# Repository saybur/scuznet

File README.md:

scuznet
=======

This is a modified version of the Scuznet board designed to fit in a
PowerBook. Also included is a small PCB for a PowerBook 100's modem 
bay. Otherwise this is fully compatible with a Scuznet V2.

Open source hardware emulating SCSI hard drives and an Ethernet adapter, for
use with vintage Macintosh computers.

# Status

The firmware is at a beta stage. There are things that are known to not work
correctly, and there are likely a large number of other bugs that have yet to
be identified and/or fixed.

If you encounter problems, please open a new issue.

# Compatibility

This implementation has some limitations by design:

1. There must be only one initiator on the bus.
2. The initiator on the bus must be at ID 7.
3. Read parity is not used. Transmission parity is provided but may be disabled
   to improve performance.

These should not be a significant problem for the target computer platform,
which for the most part has similar limitations.

# License

Except where otherwise noted, all files in this repository are available under
the terms of the GNU General Public License, version 3, available in the
LICENSE document. There is NO WARRANTY, not even for MERCHANTABILITY or
FITNESS FOR A PARTICULAR PURPOSE. For details, refer to the license.

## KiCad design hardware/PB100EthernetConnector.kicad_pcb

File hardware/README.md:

scuznet hardware
================

Provided here solely for informational purposes is a prototype hardware design
that was built for testing the scuznet firmware. This is the second revision
of the hardware, which has the following known issues.

* A USB connection is provided but there is (as yet) no hardware support for
  it. I must have lost my mind when selecting this part, it is a PITA to
  solder. Version 2.1 of the board should replace this with something easier
  to work with.
* The power connector footprint is still too big and wiggles around while
  soldering.

This version has not received significant testing yet.

# License

These files are available under the terms of the GNU General Public License,
version 3, available in the LICENSE document in the parent directory. There is
NO WARRANTY, not even for MERCHANTABILITY or FITNESS FOR A PARTICULAR PURPOSE.
For details, refer to the license.

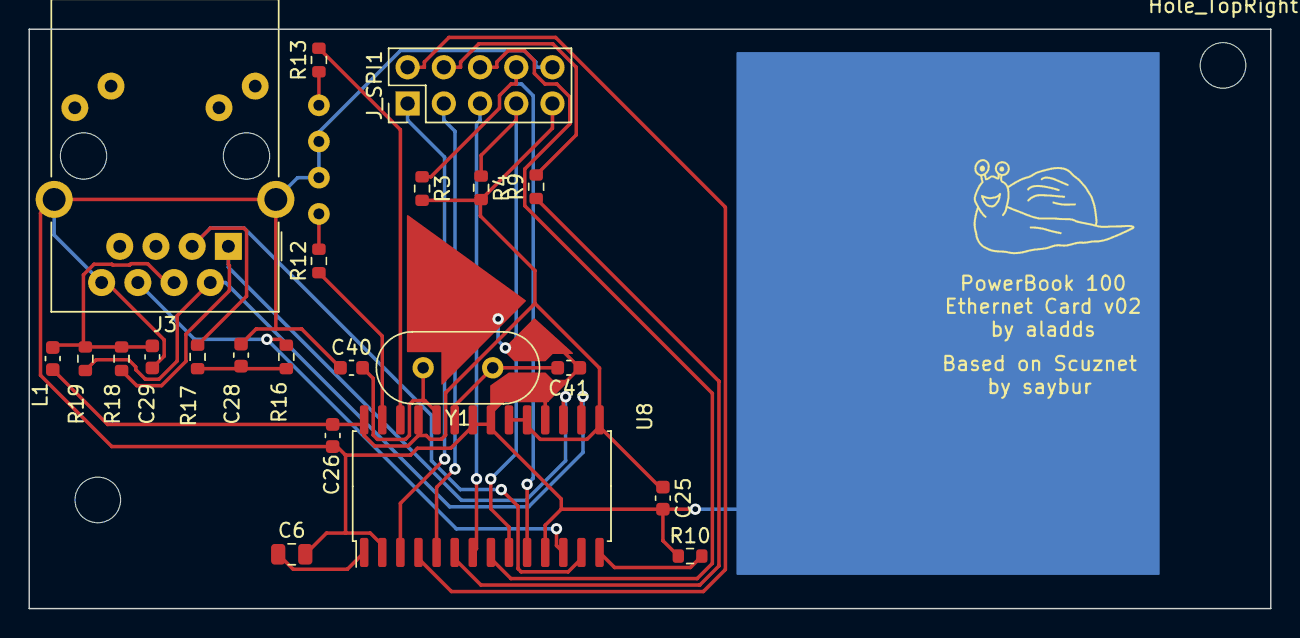
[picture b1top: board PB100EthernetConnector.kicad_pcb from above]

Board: 2 copper layers, 87.1 x 40.6 mm, 26 parts (0 on the bottom side), 25 nets.

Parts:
C6: 10uF; C_0805_2012Metric
C25, C26, C28, C29: 100nF; C_0603_1608Metric
C40, C41: 27pF; C_0603_1608Metric
Hole_BottomLeft: MountingHole_3.2mm_M3
Hole_TopRight: MountingHole_3.2mm_M3
J3: RJ45-TRANSFO; RJ45_Amphenol_RJMG1BD3B8K1ANR
JLED_A1: Conn_01x02; 2pin
JLED_B1: Conn_01x02; 2pin
J_SPI1: Conn_02x05_Odd_Even_SPI; PinHeader_2x05_P2.54mm_Vertical
L1: Ferrite_Bead; C_0603_1608Metric
R3, R4: 10K; R_0603_1608Metric
R9: 22; R_0603_1608Metric
R10: 2K32; R_0603_1608Metric
R12, R13: 330; R_0603_1608Metric
R16, R17, R18, R19: 49.9; R_0603_1608Metric
U8: ENC28J60-I/SP; SOIC-28W_7.5x17.9mm_P1.27mm
Y1: 25MHz; Crystal_HC49-4H_Vertical

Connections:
/E_CLKOUT: J_SPI1.1, U8.3
/E_MISO: J_SPI1.4, R9.2
/E_MOSI: J_SPI1.5, U8.7
/E_SCK: J_SPI1.6, U8.8
/E_WOL: J_SPI1.3, U8.5
/TPIN+: J3.R3, R17.1, U8.13
/TPIN-: J3.R6, R16.1, U8.12
/TPOUT+: J3.R1, R18.2, U8.17
/TPOUT-: J3.R2, R19.2, U8.16
/~E_CS: J_SPI1.7, R4.1, U8.9
/~E_INT: J_SPI1.2, U8.4
/~E_RST: J_SPI1.8, R3.1, U8.10
GND: C6.2, C25.2, C26.2, C28.2, C29.2, C40.1, C41.1, J3.13, J3.R8, JLED_A1.2, JLED_B1.2, J_SPI1.10, R10.1, U8.2, U8.11, U8.18, U8.21, U8.22
unnamed: C6.1, U8.1
unnamed: C28.1, R16.2, R17.2
unnamed: C29.1, J3.R4, L1.2, R18.1, R19.1
unnamed: C40.2, U8.24, Y1.2
unnamed: C41.2, U8.23, Y1.1
unnamed: JLED_A1.1, R12.2
unnamed: JLED_B1.1, R13.1
unnamed: R9.1, U8.6
unnamed: R10.2, U8.14
unnamed: R12.1, U8.27
unnamed: R13.2, U8.26
VCC: C25.1, C26.1, J_SPI1.9, L1.1, R3.2, R4.2, U8.15, U8.19, U8.20, U8.25, U8.28

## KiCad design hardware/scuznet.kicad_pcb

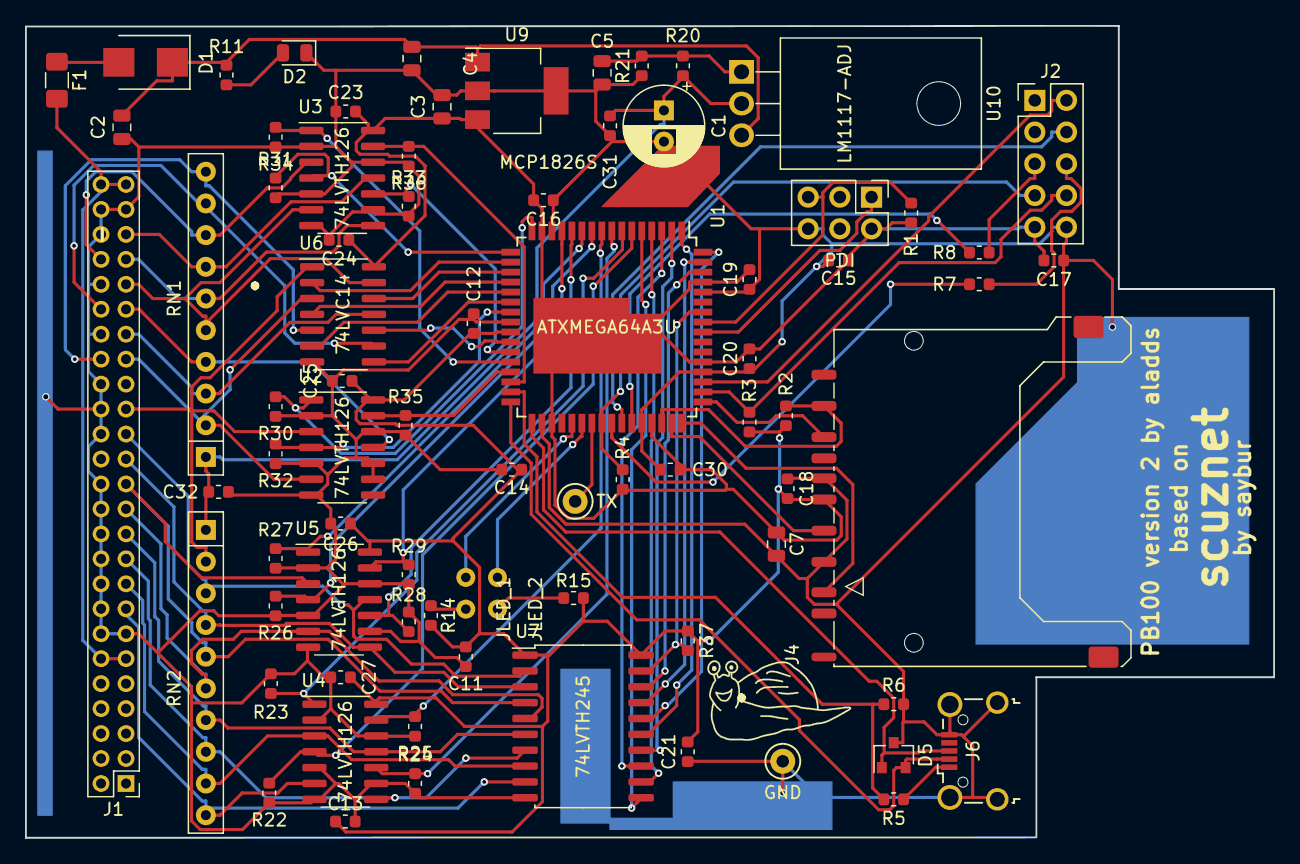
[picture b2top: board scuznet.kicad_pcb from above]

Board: 2 copper layers, 100.0 x 65.1 mm, 79 parts (0 on the bottom side), 79 nets.

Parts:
C1: 100uF; CP_Radial_D6.3mm_P2.50mm
C2, C3, C4, C5, C7: 10uF; C_0805_2012Metric
C11, C12, C13, C14, C15, C16, C17, C18, C19, C20, C21, C23, C24, C25, C26, C27, C30, C31, C32: 100nF; C_0603_1608Metric
D1: D; D_SMB
D2: LED; LED_0805_2012Metric
D5: SP0502BAHT; SOT-23
F1: Fuse; Fuse_1206_3216Metric_Pad1.42x1.75mm_HandSolder
G1***: LOGO
J1: 50PinSCSI; PinHeader_2x25_P2.00mm_Vertical
J2: Conn_02x05_Odd_Even_SPI; PinHeader_2x05_P2.54mm_Vertical
J4: SD_Card; SD_Kyocera_145638009211859+
J5: PDI; PinHeader_2x03_P2.54mm_Vertical
J6: USB_B_Micro; USB_Micro-B_Wuerth_629105150521_CircularHoles
JLED_1, JLED_2: Conn_01x02; 2pin
R1, R2, R3, R4, R5, R6: 10K; R_0603_1608Metric
R7, R8: 22; R_0603_1608Metric
R11: 330; R_0603_1608Metric
R14, R15, R21: 165; R_0603_1608Metric
R20: 150; R_0603_1608Metric
R22, R23, R24, R25, R26, R27, R28, R29, R30, R31, R32, R33, R34, R35, R36, R37: 3K3; R_0603_1608Metric
RN1, RN2: 100; R_Array_SIP10
TP1: TX; TestPoint_Keystone_5000-5004_Miniature
TP2: GND; TestPoint_Keystone_5000-5004_Miniature
U1: ATXMEGA64A3U; TQFP-64_14x14mm_P0.8mm
U2, U3, U4, U5: 74LVTH126; SOIC-14_3.9x8.7mm_P1.27mm
U6: 74LVC14; SOIC-14_3.9x8.7mm_P1.27mm
U7: 74LVTH245; SOIC-20W_7.5x12.8mm_P1.27mm
U9: MCP1826S; SOT-223-3_TabPin2
U10: LM1117-ADJ; TO-220F-3_Horizontal_TabDown

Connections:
+5V: C2.1, C4.1, D1.1, R11.2, U9.1, U10.3
/ACK: J1.37, RN1.3, U6.11
/ATN: J1.36, RN1.10, U6.5
/BSY: J1.35, RN1.2, U2.6, U6.3
/CD: J1.43, RN1.6, U3.8
/DB0: J1.15, RN2.10, U4.6, U7.9
/DB1: J1.17, RN2.9, U4.3, U7.8
/DB2: J1.19, RN2.8, U4.8, U7.7
/DB3: J1.21, RN2.7, U4.11, U7.6
/DB4: J1.23, RN2.6, U5.6, U7.5
/DB5: J1.25, RN2.5, U5.3, U7.4
/DB6: J1.27, RN2.4, U5.8, U7.3
/DB7: J1.29, RN2.3, U5.11, U7.2
/DBP: J1.31, RN2.2, U2.3, U6.1
/DIAG_TX: TP1.1, U1.39
/E_MISO: J2.4, U1.42
/E_MOSI: J2.5, R8.2
/E_SCK: J2.6, R7.2
/IO: J1.44, RN1.8, U3.3
/LED1: JLED_1.2, U1.37
/LED2: JLED_2.2, U1.38
/MSG: J1.39, RN1.4, U2.11
/RACK: U1.26, U6.10
/RATN: U1.21, U6.6
/RBSY: U1.20, U6.4
/RDB0: U1.5, U7.11
/RDB1: U1.4, U7.12
/RDB2: U1.3, U7.13
/RDB3: U1.2, U7.14
/RDB4: U1.1, U7.15
/RDB5: U1.64, U7.16
/RDB6: U1.63, U7.17
/RDB7: U1.62, U7.18
/RDBP: U1.18, U6.2
/REQ: J1.45, RN1.7, U3.11
/RRST: U1.22, U6.8
/RSEL: U1.19, U6.12
/RST: J1.40, RN1.9, U6.9
/SD_MISO: J4.7, U1.48
/SD_MOSI: J4.2, U1.49
/SD_SCK: J4.5, U1.47
/SEL: J1.41, RN1.5, U3.6, U6.13
/TBSY: R32.2, U1.23, U2.4
/TCD: R33.2, U1.27, U3.10
/TDB0: R22.2, U1.6, U4.4
/TDB1: R23.2, U1.7, U4.1
/TDB2: R24.2, U1.8, U4.10
/TDB3: R25.2, U1.9, U4.13
/TDB4: R26.2, U1.10, U5.4
/TDB5: R27.2, U1.11, U5.1
/TDB6: R28.2, U1.12, U5.10
/TDB7: R29.2, U1.13, U5.13
/TDBP: R30.2, U1.16, U2.1
/TIO: R34.2, U1.28, U3.1
/TMSG: R35.2, U1.29, U2.13
/TREQ: R36.2, U1.30, U3.13
/TSEL: R31.2, U1.17, U3.4
/~DOE: R37.1, U1.58, U7.19
/~E_CS: J2.7, R4.1, U1.40
/~E_INT: J2.2, U1.51
/~E_RST: J2.8, R3.1, U1.50
/~SD_CS: J4.1, R2.2, U1.46
GND: C1.2, C2.2, C3.2, C4.2, C5.2, C7.2, C11.2, C12.2, C13.2, C14.2, C15.2, C16.2, C17.2, C18.2, C19.2, C20.2, C21.2, C23.2, C24.2, C25.2, C26.2, C27.2, C30.2, C31.2, C32.2, D2.1, D5.3, J1.13, J1.14, J1.16, J1.18, J1.20, J1.22, J1.24, J1.26, J1.30, J1.32, J1.34, J1.38, J1.42, J1.46, J1.47, J1.48, J2.10, J4.3, J4.6, J5.6, J6.5, J6.6, R6.1, R21.2, R22.1, R23.1, R24.1, R25.1, R26.1, R27.1, R28.1, R29.1, R30.1, R31.1, R32.1, R33.1, R34.1, R35.1, R36.1, TP2.1, U1.14, U1.24, U1.34, U1.44, U1.52, U1.60, U2.2, U2.5, U2.7, U2.9, U2.10, U2.12, U3.2, U3.5, U3.7, U3.9, U3.12, U4.2, U4.5, U4.7, U4.9, U4.12, U5.2, U5.5, U5.7, U5.9, U5.12, U6.7, U7.10, U9.2
unnamed: C5.1, R20.2, R21.1, U10.1
unnamed: D1.2, F1.1
unnamed: D2.2, R11.1
unnamed: D5.1, J6.3, U1.33
unnamed: D5.2, J6.2, U1.32
unnamed: F1.2, J1.11, J1.12, J1.49, J1.50
unnamed: J5.1, U1.56
unnamed: J5.5, R1.2, U1.57
unnamed: J6.1, R5.2
unnamed: JLED_1.1, R14.2
unnamed: JLED_2.1, R15.2
unnamed: R5.1, R6.2, U1.31
unnamed: R7.1, U1.41
unnamed: R8.1, U1.43
VBUS: C1.1, C31.1, C32.1, R20.1, RN1.1, RN2.1, U10.2
VCC: C3.1, C7.1, C11.1, C12.1, C13.1, C14.1, C15.1, C16.1, C17.1, C18.1, C19.1, C20.1, C21.1, C23.1, C24.1, C25.1, C26.1, C27.1, C30.1, J2.9, J4.4, J5.2, R1.1, R2.1, R3.2, R4.2, R14.1, R15.1, R37.2, U1.15, U1.25, U1.35, U1.45, U1.53, U1.61, U2.14, U3.14, U4.14, U5.14, U6.14, U7.1, U7.20, U9.3

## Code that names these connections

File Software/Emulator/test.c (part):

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 * Human-readable versions of the reporting information.
 */
const __flash char* const __flash CMD_NAMES[] = {
	(const __flash char[]) { "ACK" },
	(const __flash char[]) { "SEL" },
	(const __flash char[]) { "RST" },
	(const __flash char[]) { "C/D" },
	(const __flash char[]) { "I/O" },
	(const __flash char[]) { "MSG" },
	(const __flash char[]) { "REQ" },
	(const __flash char[]) { "BSY" },
	(const __flash char[]) { "DBP" },
};

/*
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
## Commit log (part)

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2019-12-11 Initial project commit.
2020-01-23 Missing BOM added
2020-04-19 Alternate HDD only hardware configuration prototype.
2020-04-19 Broken out clock/debug to support future variable clock rate setting.
2020-04-22 Simplified loop for common HDD block transfer.
    Performance on my desktop went from 577kB/sec to 636kB/sec. Obviously some more room for optimization here.
2020-04-23 Tweaks to parity to squeeze out a cycle or two.
2020-04-23 Removed constant parity enable check, reorganized branches.
    Reads now 822kB/s, up from ~635kB/s. I should really use the DMA unit to properly torpedo this speed bottleneck...
2020-04-25 Variation on previous commit: less flash used, but slightly slower speed.
2020-04-26 Need more NOPs, or else 2nd byte in block read was garbage.
2020-04-26 Prev commit got patched HD SC 7.3.5 working! (adding note for later)
2020-04-26 Fix to INQUIRY length per warnings from sg_inq
2020-10-22 Add blinking fail for brown-out reset
2020-10-23 Start of post-assembly board testing firmware.
2020-10-24 Try to fix fail detect on working board
2020-10-24 testing main.c was messy, split testing code into separate files.
2020-10-24 Adding RDBP definition for testing code.
2020-10-24 /SEL has its own driver, no connection on that one needed.
2020-10-24 Oops, off by 1; PHY testing working OK now with loopback dongle.
2020-10-24 Tried to clarify README language.
2021-03-06 Added delay for bus free following DISCONNECT
2021-04-04 Add files via upload
    Scuznet-Daynaport fork of Scuznet that support emulation of Daynaport SCSI ethernet device versus Nuvolink. See Readme
2021-04-04 Add files via upload
    Updated Readme
2021-05-26 Hardware revision 2.
2021-06-06 Delay needed from data /OE assertion when no external latch is present.
2021-06-06 Ask for hardware revision by default like the main firmware.
2021-06-10 Added notes for HD SC support and the hardware revision flag.
2021-06-13 Never got around to making this hypothetical board.
2021-06-13 No longer optional to include both HDD/Ethernet support.
    This will hopefully streamline the configuration changes coming down the pipeline.
2021-06-16 Change from Petit FatFs to full FatFs library.
2021-06-18 Removed the old PHY USART/block transfer calls, this will be different going forward.
2021-06-18 Moved from static to automatic allocation of some buffers.
2021-06-18 Added function prototypes for FatFs and documented intended changes.
2021-06-18 Broken FatFs multi-write support.
    This has a partially implemented multi-write call. This works only for
    files less than about 32K or so, which makes me think the issue is
    probably something to do with cluster boundaries and how the caches switch
    around when you hit them. I haven't been able to figure this out, so I'm
    going to try switching to the much simpler Petit FatFs and trade my
    problems out :)
2021-06-18 Restoring Petit FatFs R0.03a
2021-06-18 Copied over FatFs based README and updated for planned changes to Petit.
2021-06-19 Rearranged the partial write function.
2021-06-19 Snapshot of current work, do not use in the future.
    Things are not working for the multiple writes - any time I activate any part of the new code, it immediately breaks things. Not sure what's malfunctioning.
2021-06-19 DMA writes now work!
    SCSI Evaluator on my IIci went from ~100KB/s to ~900KB/s, which is nice.
    The "+ cs" on the "sect" variable appears to have been the underlying
    problem.
2021-06-19 pf_mread() implementation
    Does not use the multi-read under the hood. ~300KB/s on IIci.
2021-06-20 Non-DMA CMD18 reads working. Speed is ~500KB/s on IIci.
2021-06-20 Removed full FatFs.
2021-06-20 Configuration now done via scuznet.ini
    Hard drive sizing to the provided image file is not working yet, still
    fixed at 500MB.
2021-06-20 Configured hard drive size now based on image size.
2021-06-22 Support added for multiple emulated hard drives.
2021-06-23 Fixed case where /SEL still active during check caused unexpected bus release.
    Also fixed bug where hdd_main() check was inverted, oops.
2021-06-23 HDD size protection and reporting of bad command opcodes.
2021-06-23 There is some funky code here, need to fix later.
2021-06-23 Experimental support for vetoing native volumes > memory card size.
    I haven't tried pushing this limit yet. Needs to be checked later.
2021-06-23 Cleaned up 'raw' entry description.
2021-06-24 Shift from 64A3U to 192A3U as "default" MCU
2021-06-24 Re-adding FatFs R0.14b
2021-06-25 Very basic working implementation of FatFs.
    This does not implement multi-sector reads and writes and is very slow.
2021-06-26 Preliminary f_mwrite() support.
2021-06-26 Files now opened during HDD setup and left that way.
    With the only access being through f_mread() and f_mwrite(), I think it's OK to use the TINY configuration without a performance penalty, but I'm not 100% sure about that. Needs more testing.
2021-06-26 Adding ffunicode.c for potential exFAT support.
2021-06-26 General cleanup of HDD code.
2021-06-26 Removed the modified Petit FatFs, replaced by full FatFs.
2021-06-26 exFAT / LFN auto-enabled if not on the 64A3U.
2021-06-26 Incorporating @superjer2000 INQUIRY work.
2021-06-27 Update ffconf.h
    Fixes compile issue for me Makefile doesn't include AVR
2021-06-27 Tweaks to base ENC filter control.
2021-06-27 Broke out command / MAC handler for each device.
2021-06-27 Main loop now handles the link bus disconnect response.
2021-06-27 No more direct USART manipulation in link.c
2021-06-27 Moving away from the "one byte pending" USART approach.
    This was making my head hurt. The new approach is slightly slower but should be easier to understand.
    This also leaves the RX part of the USART enabled during write ops. As I recall, this was an issue ages ago when I was experimenting with DMA transactions, which may come back again later.
2021-06-28 Configure network via ini file, and more debugging symbols.
    Performance on Dayna is awful, 2KB/s on my IIci. Needs more debugging.
2021-06-28 Silence compiler warning when using ANSI characters.
2021-06-29 Support for creating image files via configuration.
2021-06-29 Support either MCU definition style.
    This is likely a toolchain difference. Not sure this is capturing all options yet.
2021-06-29 Moving pending problems to the issue tracker.
2021-06-29 Most ENC calls now return an ENCSTAT result.
2021-06-29 Preliminary support for concurrency on the Ethernet subsystem.
2021-06-29 The configuration part of the HDD setup is now back in hdd.c
2021-06-30 Major, untested, and incomplete changes to networking.
    Move all ENC code over to net.c, and setup for making packet header reading interrupt-driven.
2021-07-01 Ongoing development of net code; not ready for testing yet.
2021-07-01 /E_INT ISR now disables itself after being invoked.
    It will be re-enabled when safe to do so.
2021-07-02 Now keeping only the first header in memory (still untested).
2021-07-03 Removed some leftover debugging code.
2021-07-03 More bulk networking work.
2021-07-03 Standardized the fatal flash-codes.
2021-07-03 config_read() now directly fails, and added # bytes trailing debug symbols.
    Also added README entries for the fatal flash codes.
2021-07-03 Adding a debug flag during reset.
2021-07-03 Changes to handle stalled transmit packets.
    This has not completely solved the problem.
2021-07-03 Redid how transmission check worked.
    Feels more stable. Did 30MB in 180 seconds, ~167KB/s, which is a significant improvement. It also didn't have any obvious stalls during the transfer.
2021-07-04 FAT contiguous check is now done in the background.
    This seems to work well thus far: FAT is used until check is complete, and my system can now boot off the volumes.
2021-07-04 Made some progress figuring out what CMD 0x09 is doing.
2021-07-04 Fixed implementation error with Nuvo filtering.
2021-07-04 HTML tool for calculating ENC28J60 / 8390 hash table values.
2021-07-04 Hardware V2 now uses amber LED for activity, green for power indication.
2021-07-05 Test routine now part of main codebase.
    Documentation now on the wiki.
2021-07-05 Protocol now documented on the wiki instead of the main repository.
2021-07-05 Include test.c when building.
2021-07-05 Some content moved to the wiki.
2021-07-07 Need to leave high interrupts on to allow safe /RST behavior.
2021-07-07 'raw' mode access removed from configuration options.
2021-07-07 Re-cooked the f_contiguous call to reduce f_lseek() usage.
    There wasn't a good reason to do it the original way. New method invokes it just once, so the check now clears in half the time. Still isn't fixing the bootup issue.
2021-07-07 Wrong file pointer, which could be bad.
2021-07-08 MTU to 1518 (was previously 1536 per reset value)
2021-07-09 Extend the reselection delay from ~250us to ~5000us.
    This seems to have significantly increased stability with FTP transfers.
2021-07-09 Experimental single-TX buffer instead of dual-TX, for more RX space.
2021-07-09 Have Nuvolink accept broadcast packets by default, like Dayna.
    Without this ARP resolution for MacTCP was dependent on AppleTalk being enabled.
2021-07-14 Increased debugging output for the hard drive emulator.
2021-07-16 Fix memory card DMA read underflows.
    Before this, if a byte got missed the DMA read channel would never end, stalling the system.
    Now ignored during data writes, where the only byte of interest is the last one anyway and already has a check.
    During data reads underflow triggers a soft error and should now resolve itself.
2021-07-17 Applying 1x TX buffer change.
    This improves RX performance with TCP quite a bit.
    So far this appears to have only a minor impact to TX.
    RX with FTP on IIsi test system +50%, TX basically identical.
2021-07-17 Added stack usage detection.
    There is heap usage via the string library, so this will always report 0.
    Will be fixed in a later commit.
2021-07-17 Moved config strings to flash memory, saving ~114 bytes of SRAM.
2021-07-17 Prevent race condition during DMA unit startup.
2021-07-18 Filename now allocated on the stack and limited to 8.3 format.
2021-07-18 Removed old debugging statement.
2021-07-18 Brownout is now 7 long / 2 short.
2021-07-18 Trying to reduce the memory consumption of the INI library.
2021-07-18 Memory card buffers now available for other code to use.
2021-07-18 Use the global buffer for some HDD calls.
2021-07-18 Moved ID and command buffer onto the stack.
2021-07-18 Read buffer to stack.
2021-07-18 Simplification of the logic error reporting system.
    This helps hide more of the low-level details and frees some more memory.
2021-07-24 Added -DFORCE_NUVO and -DFORCE_DAYNA to override config during development.
2021-07-27 Experimental assembly routines for SCSI read/write.
2021-07-28 Atomic protection on bus fetch isn't strictly required.
    +50KB/s write performance without these on a IIci.
2021-07-31 Experimental PHY timeout implementation.
2021-08-07 Now compiles on both V1 and V2 boards.
2021-09-11 Added bootloader based on mcxboot.
2021-09-20 Experimental and untested CD-ROM support.
2021-09-21 MODE SENSE/SELECT to separate compilation unit w/ SCSI CD-ROM included.
2022-05-29 Moved Source Code Into Source Folder
2022-05-29 Formatted Status
2022-05-29 Added License Badge
2022-05-29 Added GitIgnore
2022-05-29 Added Quicklinks
2022-06-16 Added the 3D case Chopsticks designed :)
2022-07-13 Delete lib directory
    Refer to main scuznet repo for software.
2022-07-13 Delete Makefile
    Refer to main scuznet repo for software.
2024-07-15 Finally getting around to adding a .gitignore
2024-07-16 Adding support for downloading files with the toolbox API.
2024-08-05 added case Front Panel for builds without USB

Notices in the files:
Software/Emulator/test.c:
Copyright (C) 2019 saybur
scuznet is free software: you can redistribute it and/or modify
it under the terms of the GNU General Public License as published by
the Free Software Foundation, either version 3 of the License, or
(at your option) any later version.
